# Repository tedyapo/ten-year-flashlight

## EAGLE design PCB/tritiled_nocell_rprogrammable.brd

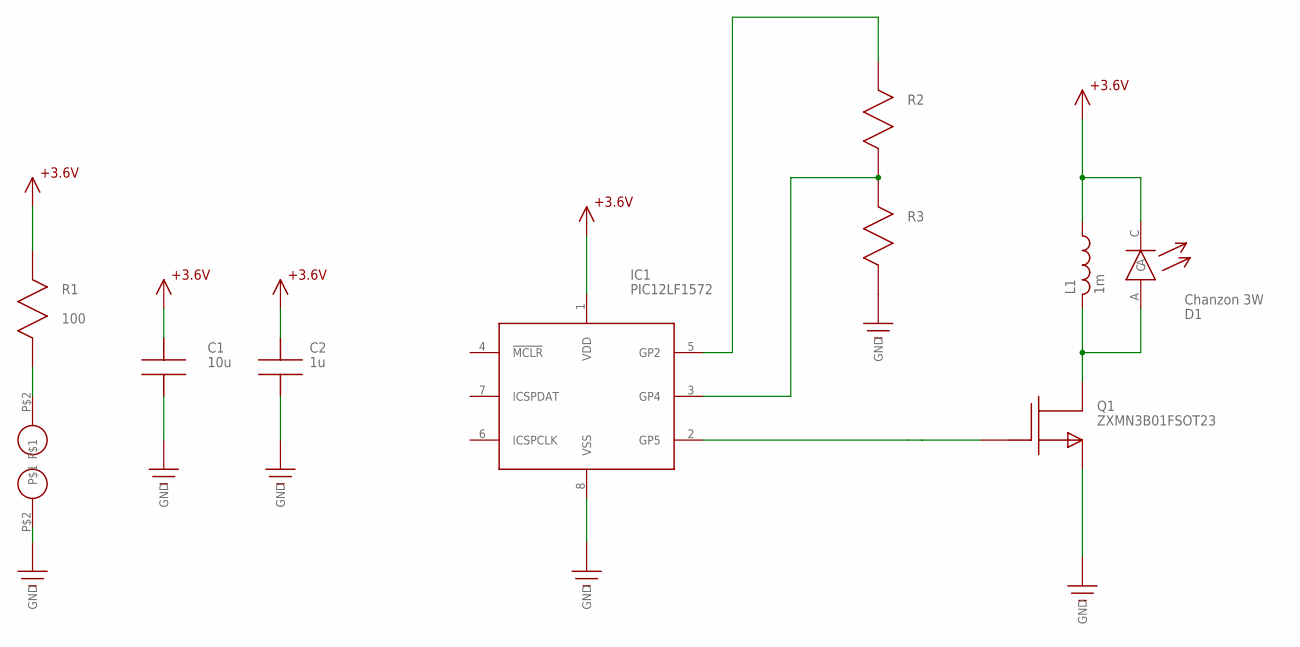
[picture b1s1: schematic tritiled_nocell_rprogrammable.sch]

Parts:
C1: 10u; 1206
C2: 1u; C0603
D1: Chanzon 3W; LED_3W
IC1: PIC12LF1572; SOIC8
L1: 1m; SRR6028_INDUCTOR
Q1: ZXMN3B01FSOT23; SOT-23
R1: 100; R1206
R2, R3: R1206
U$7, U$9: ICSP_PAD

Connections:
+3.6V: C1.P$1, C2.P$1, D1.C, IC1.1 (VDD), L1.P$1 (1), R1.P$1
GND: C1.P$2, C2.P$2, IC1.8 (VSS), Q1.2 (S), R3.P$2, U$9.P$2
unnamed: IC1.3 (GP4), R2.P$2, R3.P$1
unnamed: R1.P$2, U$7.P$2
unnamed: IC1.5 (GP2), R2.P$1
unnamed: D1.A, L1.P$2 (2), Q1.3 (D)
unnamed: IC1.2 (GP5), Q1.1 (G)

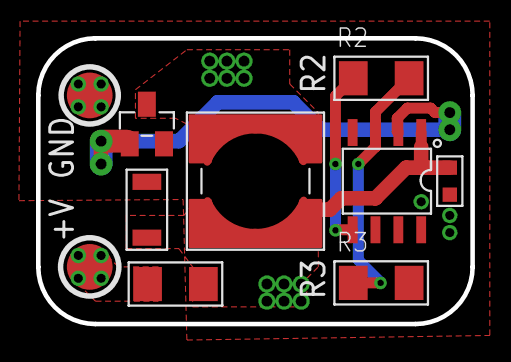
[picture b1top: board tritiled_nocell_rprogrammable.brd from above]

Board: 2 copper layers, 24.1 x 15.9 mm, 11 parts (1 on the bottom side), 7 nets.

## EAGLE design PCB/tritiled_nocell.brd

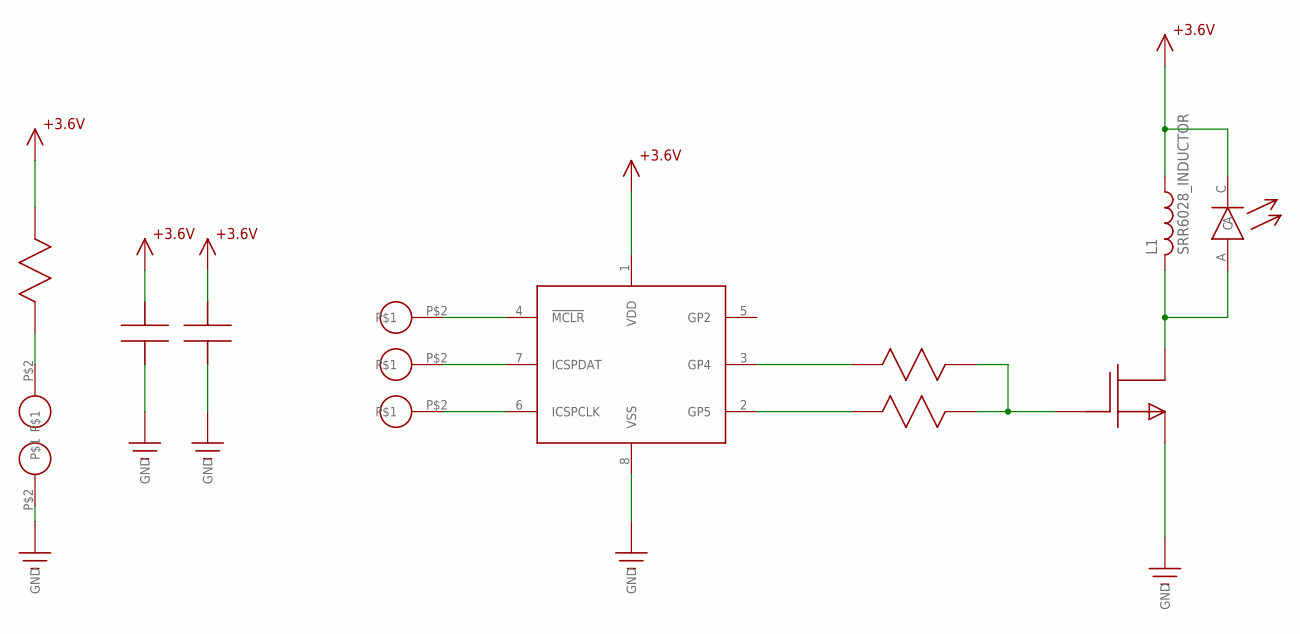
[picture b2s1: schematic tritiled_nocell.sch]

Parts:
L1: SRR6028_INDUCTOR
U$1: PIC12LF1571; SOIC8
U$7, U$9, U$17, U$18, U$19: ICSP_PAD
U$10: R1206
U$12: LED_3W
U$16: ZXMN3B01FSOT23; SOT-23
U$20: C1206; 1206
U$21: C0603
U$22, U$23: R0603

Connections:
+3.3V: L1.P$1 (1), U$1.1 (VDD), U$10.P$1, U$12.C, U$20.P$1, U$21.P$1
GND: U$1.8 (VSS), U$9.P$2, U$16.2 (S), U$20.P$2, U$21.P$2
unnamed: U$1.4 (!MCLR!), U$18.P$2
unnamed: U$7.P$2, U$10.P$2
unnamed: U$1.7 (ICSPDAT), U$19.P$2
unnamed: U$1.6 (ICSPCLK), U$17.P$2
unnamed: L1.P$2 (2), U$12.A, U$16.3 (D)
unnamed: U$1.3 (GP4), U$23.P$1
unnamed: U$1.2 (GP5), U$22.P$1
unnamed: U$16.1 (G), U$22.P$2, U$23.P$2

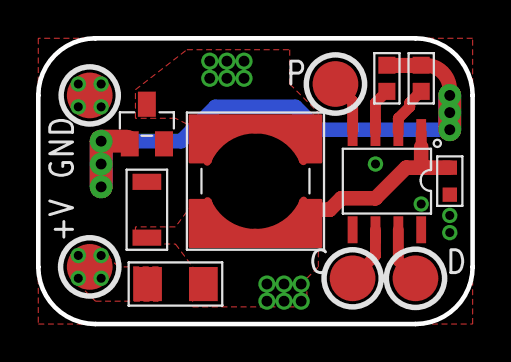
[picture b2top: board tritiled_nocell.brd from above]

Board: 2 copper layers, 24.1 x 15.9 mm, 14 parts (1 on the bottom side), 10 nets.

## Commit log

2020-07-19 checkpoint
